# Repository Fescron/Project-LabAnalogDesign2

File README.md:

# Project-LabAnalogDesign2

<br/>

The goal of this lab was to design a 5 - 9V to 3,3V (500 mA min) buck converter from the ground up. We had to start from a given chip (`RT8259GE`) and create the rest ourselves.

Careful layout considerations were taken to lead to an optimal design. The `0Ω` resistor is not on the schematic but only on the board layout. It's footprint was used to *jump* over the feedback track so everything is on the top layer. A via to GND is placed around it as well for redundancy.

- `JP1` can be used to disable the buck converter.
- `JP2` can be used to bypass the sense resistor `R3` (measures the diode current).
- A lot of test points (`TPx`) are given to be able to measure different voltages.
- `C4` and `C5` are footprints for extra capacitors if the signals have too much ripple.
<!-- fix vertical spacing -->
- VIN: 4,5 - 24 V
- VOUT: 3,3 V @ 1,2 A max
<!-- fix vertical spacing -->
- Click [here](hardware/dc-dc-3-3V-RT8259GE/dc-dc-3-3V-RT8259GE.pdf) to go to the **schematic**.
- Click [here](documentation/report/AnaloogOntwerp2-Labo-BuckConverter-Brecht-Arno.pdf) to go to the **report** (Dutch).

<br/>

 &nbsp; &nbsp; 

<br/>

## BOM

| Component | Value                       | Footprint     | Other               | Ordering                                                                                                                                         |
| --------- | --------------------------- | ------------- | ------------------- | ------------------------------------------------------------------------------------------------------------------------------------------------ |
| U1        | RT8259GE                    | SOT-23-6      | Richtek             |                                                                                                                                                  |
| C1, C4    | 10 µF                       | 1206          | (X7R), 50V, 10%     | [Mouser.be](https://www.mouser.be/ProductDetail/Taiyo-Yuden/UMK316BBJ106KL-T?qs=sGAEpiMZZMs0AnBnWHyRQC2E6Mcmylam9RgrENSytztpBCepHfvewA%3D%3D)    |
| C2, C5    | 22 µF                       | 1206          | X7R, 10V, 10%       | [Mouser.be](https://www.mouser.be/ProductDetail/Taiyo-Yuden/LMK316AB7226KL-TR?qs=sGAEpiMZZMs0AnBnWHyRQNbg85K4ab%2F3vBf6FXuF68A%3D)               |
| C3        | 10 nF = 0,01 µF             | 0805          | X7R, 50V, 10%       | [Mouser.be](https://www.mouser.be/ProductDetail/Wurth-Elektronik/885012207092?qs=sGAEpiMZZMs0AnBnWHyRQEGbLOF2VP1iBKezlgXLZvo%2F8tItKANG8A%3D%3D) |
| D1        | If = 2A Vr = 40V Vf = 0,43V | SMA/SMB       |                     | [Mouser.be](https://www.mouser.be/ProductDetail/ON-Semiconductor/MBRS2040LT3G?qs=sGAEpiMZZMtQ8nqTKtFS%2FCKUxMvjsmGzEfxVIbeME%2FY%3D)             |
| L1        | 4,7 µH                      | NR8040        | Taiyo Yuden         | [Mouser.be](https://www.mouser.be/ProductDetail/Taiyo-Yuden/NR8040T4R7N?qs=sGAEpiMZZMsg%252By3WlYCkU5iuzh4MJmq0qQohkARpSRw%3D)                   |
| R1        | 62 kΩ                       | 0805          | 0,5%                | [Mouser.be](https://www.mouser.be/ProductDetail/Susumu/RR1220P-623-D?qs=sGAEpiMZZMtlubZbdhIBIIeqUIwQIz3%2F4suNfbqaJx0%3D)                        |
| R2        | 19,6 kΩ                     | 0805          | 0,5%                | [Mouser.be](https://www.mouser.be/ProductDetail/Susumu/RR1220P-1962-D-M?qs=sGAEpiMZZMtlubZbdhIBIIeqUIwQIz3%2FtET9VVF0mUY%3D)                     |
| R3        | 0,1 Ω = 100 mΩ              | 1206          | 1%                  | [Mouser.be](https://www.mouser.be/ProductDetail/Ohmite/KDV12FR100ET?qs=sGAEpiMZZMtlubZbdhIBIFv9D87cWnlaxTC7ytBtffo%3D)                           |
| 0Ω        | 0 Ω                         | 1206          |                     | [Mouser.be](https://www.mouser.be/ProductDetail/Yageo/RC1206JR-070RL?qs=sGAEpiMZZMtlubZbdhIBIMHu9P6GKOabM4IOLvph3MY%3D)                          |
| J1, J2    | PTSA_1,5/_2-3,5-Z_BK        | Pitch: 3,5 mm | 2 contacts, 250V 2A | [Mouser.be](https://www.mouser.be/ProductDetail/Phoenix-Contact/1751765?qs=sGAEpiMZZMvZTcaMAxB2AOnzhHajZlLEGRULH%2FxUGnk%3D)                     |

> **WARNING:** The pinout of J1 and J2 is reversed due to a footprint error (wrong top/bottom view). The Phoenix Contact connectors can however be manually separated and put back together in a way that they do fit on the board.

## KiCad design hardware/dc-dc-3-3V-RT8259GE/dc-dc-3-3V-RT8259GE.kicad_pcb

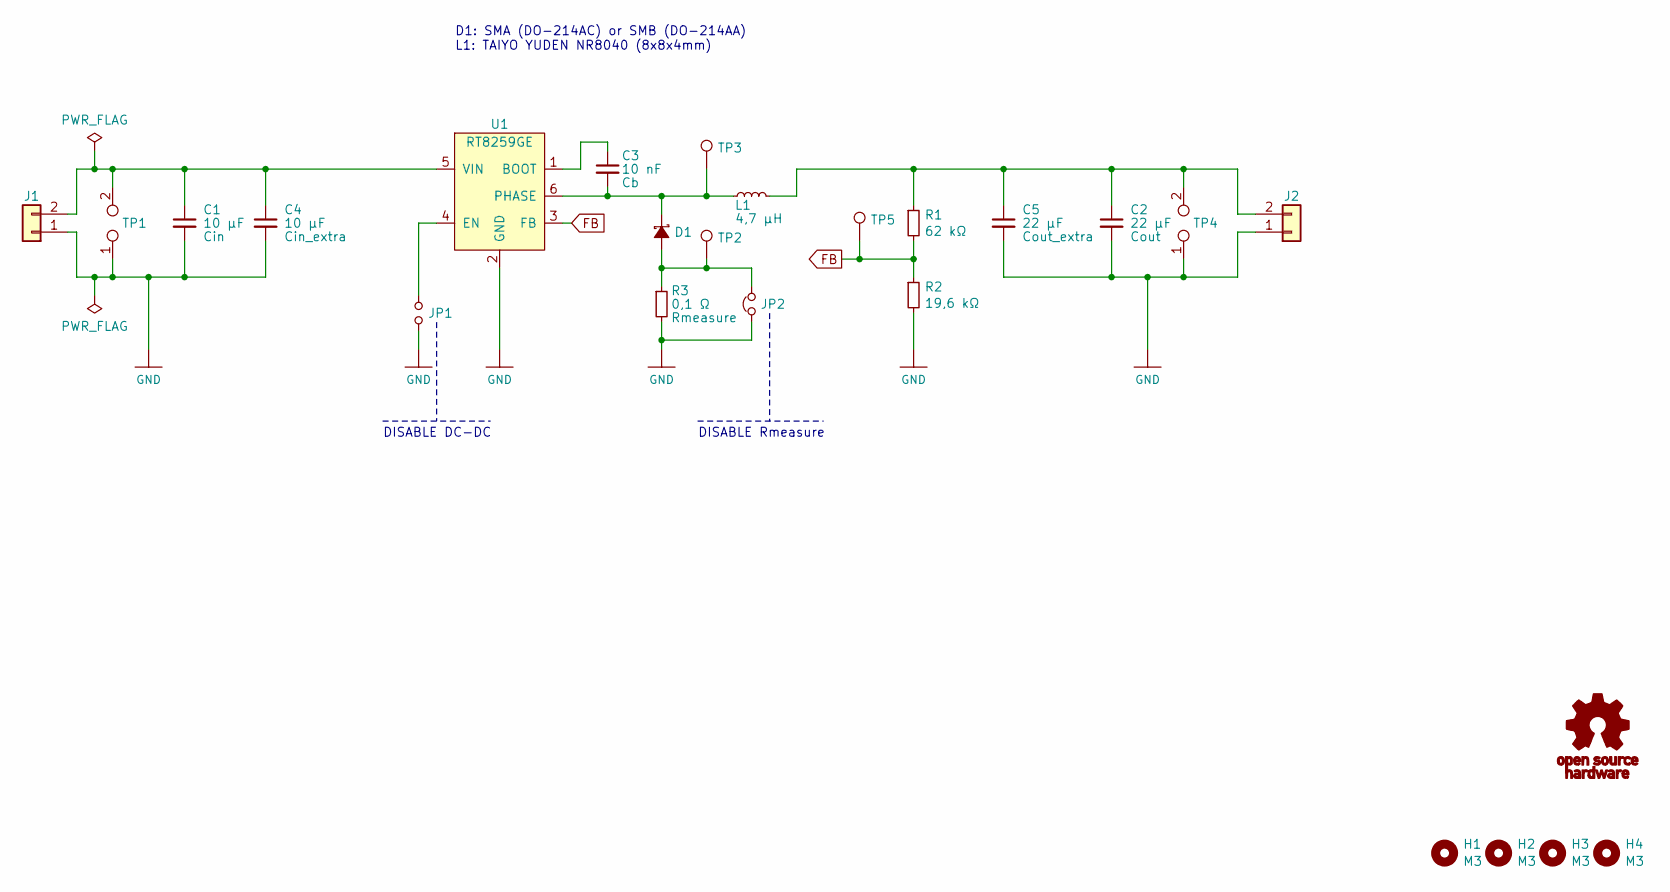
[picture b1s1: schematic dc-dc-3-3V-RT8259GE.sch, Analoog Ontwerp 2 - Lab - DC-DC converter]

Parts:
C1, C4: 10 µF; C_1206_3216Metric_Pad1.42x1.75mm_HandSolder
C2, C5: 22 µF; C_1206_3216Metric_Pad1.42x1.75mm_HandSolder
C3: 10 nF; C_0805_2012Metric_Pad1.15x1.40mm_HandSolder
D1: D_Schottky_Small_ALT; D_SMA-SMB_Universal_Handsoldering
G1: Symbol_OSHW-EEVBLOG_SPFMDBC_10mm; OSHW-Logo_5.7x6mm_SolderMask
H1, H2, H3, H4: M3; MountingHole_3.2mm_M3
J1, J2: Conn_01x02; PhoenixContact_PTSA_1,5_2-G-3,5_1x02_P3.50mm_Angled
JP1: Jumper_NO_Small; PinHeader_1x02_P2.54mm_Vertical
JP2: Jumper_NC_Small; PinHeader_1x02_P2.54mm_Vertical
L1: 4,7 µH; L_Taiyo-Yuden_NR-80xx_HandSoldering
R1: 62 kΩ; R_0805_2012Metric_Pad1.15x1.40mm_HandSolder
R2: 19,6 kΩ; R_0805_2012Metric_Pad1.15x1.40mm_HandSolder
R3: 0,1 Ω; R_1206_3216Metric_Pad1.42x1.75mm_HandSolder
TP1, TP4: TestPoint_2Pole; PinHeader_1x02_P2.54mm_Vertical
TP2, TP3, TP5: TestPoint; PinHeader_1x01_P2.54mm_Vertical
U1: RT8259GE; SOT-23-6_Handsoldering

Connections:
FB: R1.2, R2.1, TP5.1, U1.3 (FB)
GND: C1.2, C2.2, C4.2, C5.2, J1.1, J2.1, JP1.1, JP2.1, R2.2, R3.2, TP1.1, TP4.1, U1.2 (GND); also elsewhere on the board
unnamed: C1.1, C4.1, J1.2, TP1.2, U1.5 (VIN)
unnamed: C2.1, C5.1, J2.2, L1.2, R1.1, TP4.2
unnamed: C3.1, U1.1 (BOOT)
unnamed: C3.2, D1.1 (K), L1.1, TP3.1, U1.6 (PHASE)
unnamed: D1.2 (A), JP2.2, R3.1, TP2.1
unnamed: JP1.2, U1.4 (EN)

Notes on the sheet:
DISABLE DC-DC
DISABLE Rmeasure
D1: SMA (DO-214AC) or SMB (DO-214AA) L1: TAIYO YUDEN NR8040 (8x8x4mm)

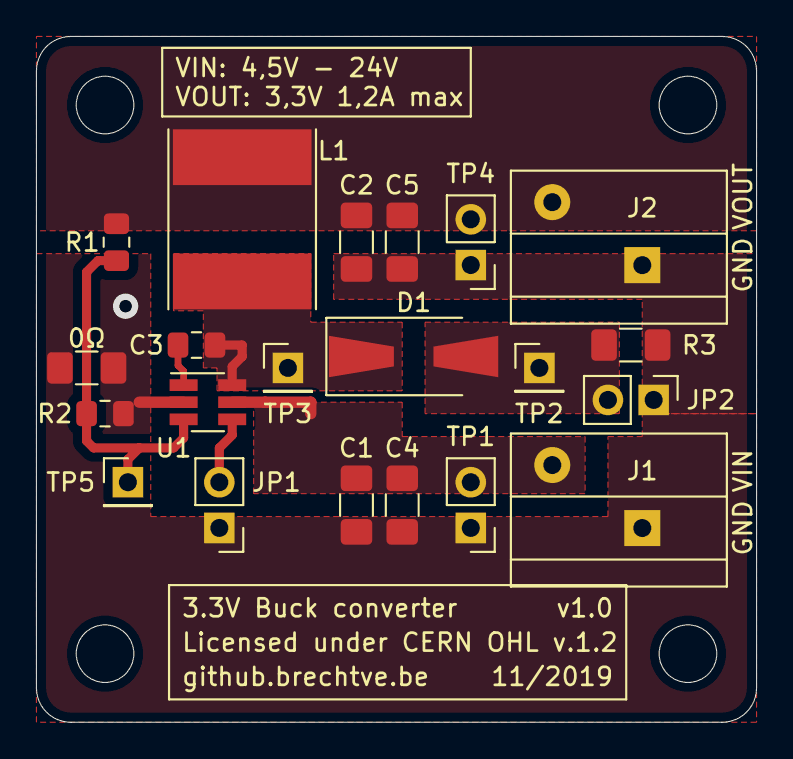
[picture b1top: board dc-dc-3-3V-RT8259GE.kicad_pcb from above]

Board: 2 copper layers, 40.0 x 38.1 mm, 26 parts (0 on the bottom side), 8 nets.

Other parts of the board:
0Ω: R_1206_3216Metric_Pad1.42x1.75mm_HandSolder

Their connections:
GND: 0Ω.1, 0Ω.2; also elsewhere on the board

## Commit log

2019-11-26 Added licence
2019-11-26 Added datasheet
2019-11-26 Added pictures
2019-11-26 Added schematic and board layout
2019-12-03 Updated readme with note about wrong footprint
2019-12-03 Updated cache
2019-12-15 Added report

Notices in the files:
README.md:
License: CERN OHL v.1.2
hardware/dc-dc-3-3V-RT8259GE/dc-dc-3-3V-RT8259GE.kicad_pcb:
Licensed under CERN OHL v.1.2
